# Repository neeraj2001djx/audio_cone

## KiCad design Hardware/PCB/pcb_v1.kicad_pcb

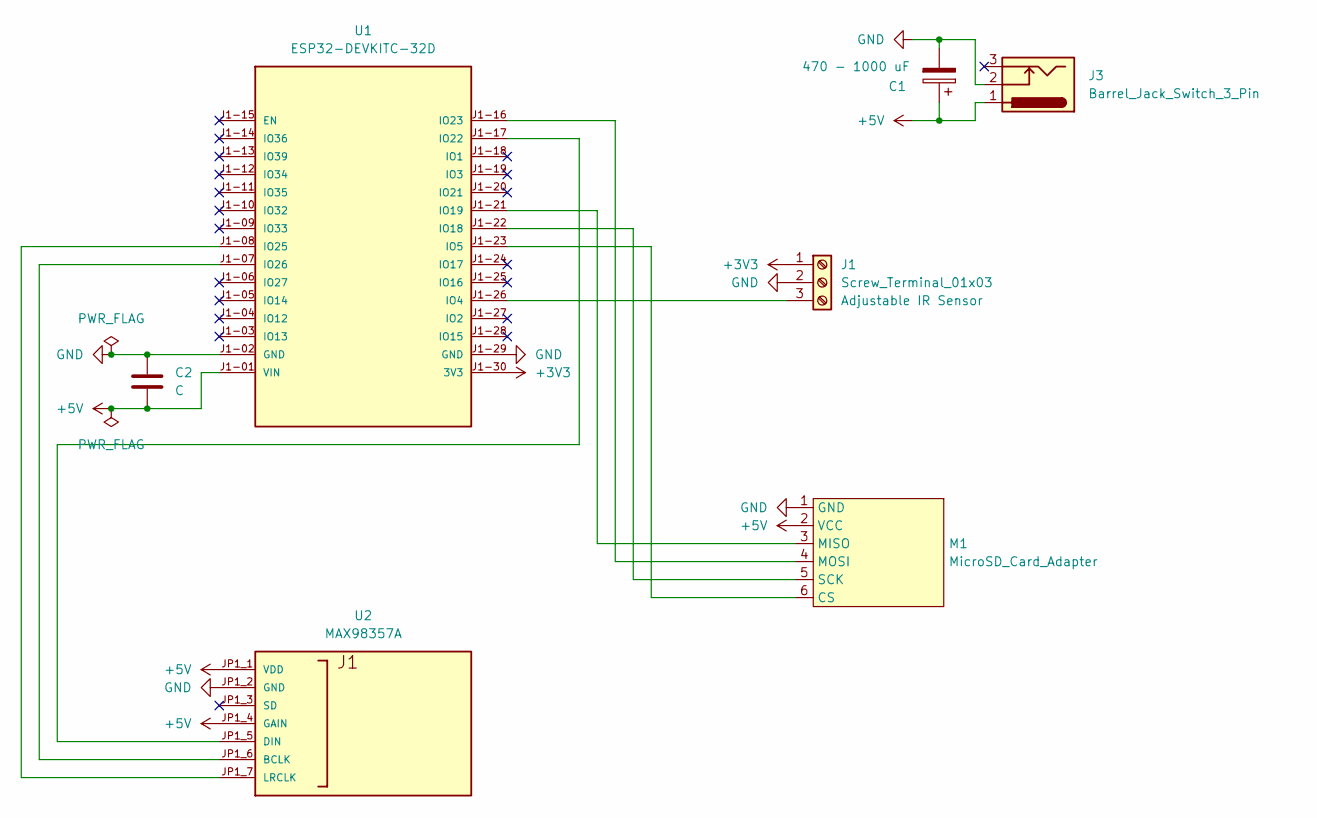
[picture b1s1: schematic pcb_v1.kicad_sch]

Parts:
C1: 470 - 1000 uF; Capacitor_Horizontal_L12xR8xP3.5
C2: C; C_Disc_D5.0mm_W2.5mm_P2.50mm
J1: Screw_Terminal_01x03; JST_1x03_P2.50mm_Horizontal
J3: Barrel_Jack_Switch_3_Pin; BarrelJack_Horizontal
M1: MicroSD_Card_Adapter
U1: ESP32-DEVKITC-32D; ESP32_NODEMCU
U2: MAX98357A

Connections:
+3V3: J1.1, U1.J1-30 (3V3)
+5V: C1.1, C2.2, J3.1, M1.2 (VCC), U1.J1-01 (VIN), U2.JP1_1 (VDD), U2.JP1_4 (GAIN)
GND: C1.2, C2.1, J1.2, J3.2, M1.1 (GND), U1.J1-02 (GND), U1.J1-29 (GND), U2.JP1_2 (GND)
unnamed: J1.3, U1.J1-26 (IO4)
unnamed: M1.6 (CS), U1.J1-23 (IO5)
unnamed: M1.3 (MISO), U1.J1-21 (IO19)
unnamed: M1.4 (MOSI), U1.J1-16 (IO23)
unnamed: M1.5 (SCK), U1.J1-22 (IO18)
unnamed: U1.J1-17 (IO22), U2.JP1_5 (DIN)
unnamed: U1.J1-08 (IO25), U2.JP1_7 (LRCLK)
unnamed: U1.J1-07 (IO26), U2.JP1_6 (BCLK)

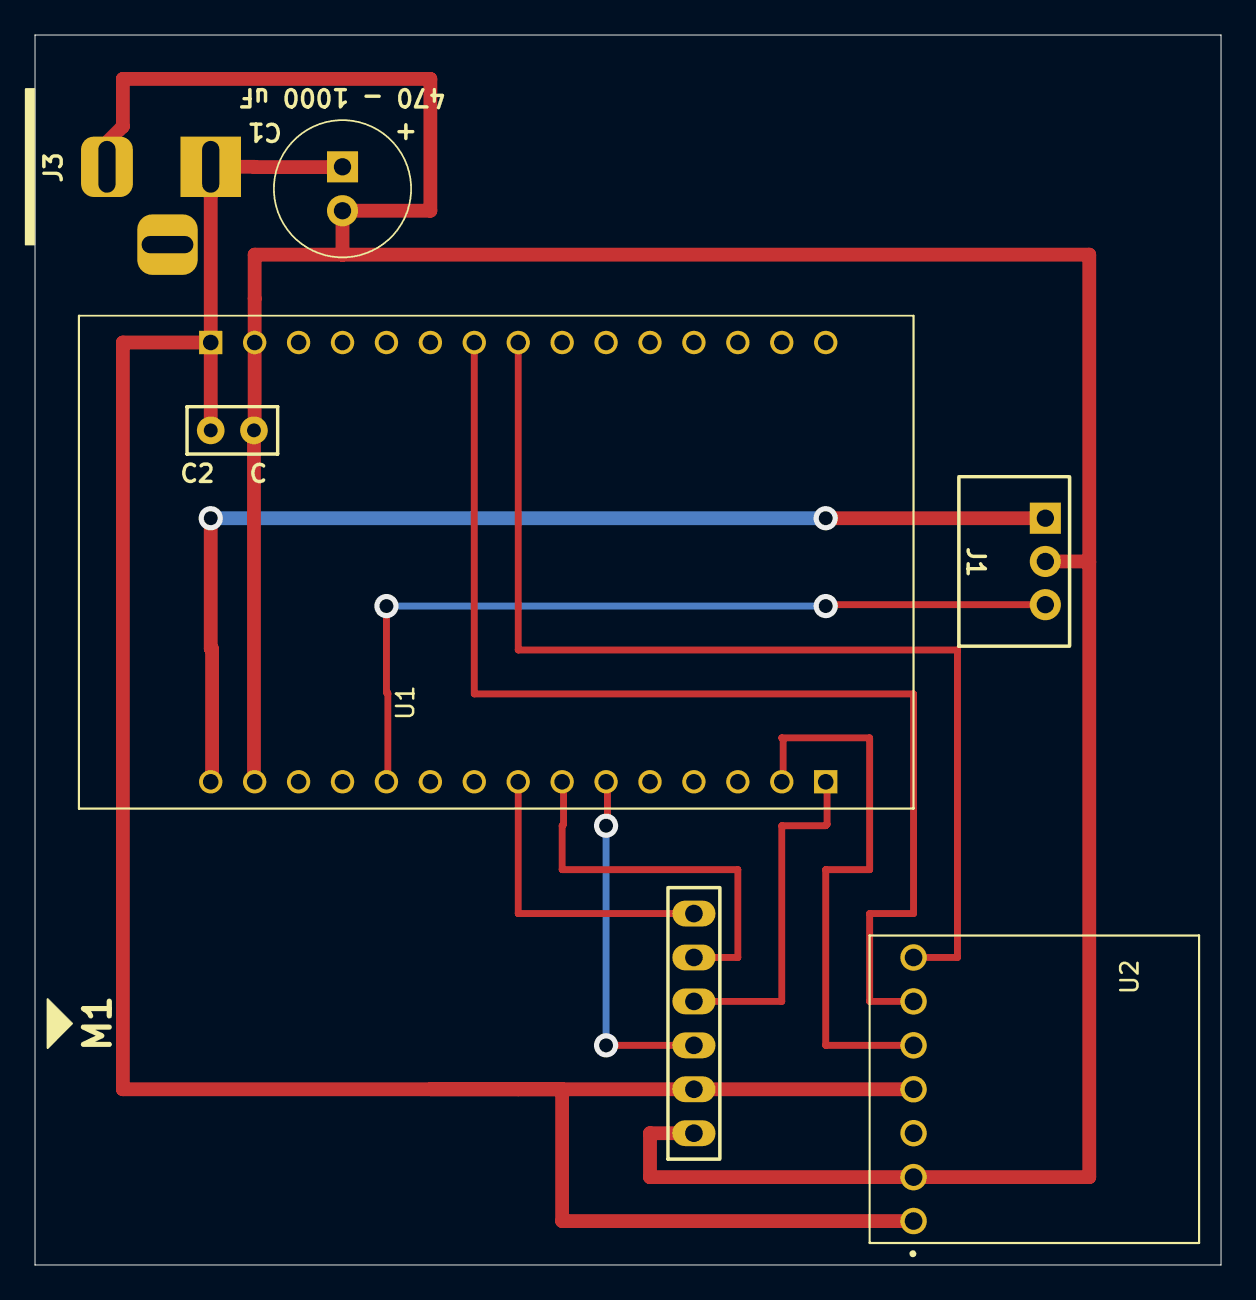
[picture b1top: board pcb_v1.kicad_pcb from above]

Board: 2 copper layers, 68.6 x 71.1 mm, 7 parts (0 on the bottom side), 11 nets.

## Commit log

2026-03-15 2026-03-16
    1. Plays audio.wav from SD card when button is pressed.
    2. Stops audio playback when button is released.
    3. Downloads new audio file from server via HTTP when MQTT command is received.
    4. Saves downloaded audio to SD card as audio.wav.
    5. Controls playback volume through MQTT topic.
    6. Publishes device state (idle, playing, downloading) to MQTT.
2026-03-15 2026-03-16
2026-03-21 2026-03-21.ino
